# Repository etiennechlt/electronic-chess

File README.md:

# Échiquier électronique automatique à détection LC

Échiquier physique qui identifie chaque pièce (type et couleur) par un
résonateur LC passif logé dans sa base, arbitre les coups (roque,
prise en passant, promotion incluse), joue contre un moteur d'échecs
ou en ligne, et fonctionne sur batterie. Plateau fin de 44 cm et
21 mm d'épaisseur ; le déplacement des pièces par aimant sur portique
CoreXY est une base optionnelle qui se substitue au fond plat. Le
STM32G474 est maître, un ESP32-S3 sert de pont radio (WiFi, BLE vers
l'horloge à bascule séparée), le Raspberry Pi Zero 2 W est optionnel.

## Principe de détection

Chaque pièce porte une bobine plate de 45 µH et un condensateur C0G
1 % de la série E12 qui fixe sa classe (12 valeurs, 217 à 613 kHz).
Chaque case excite en large bande par un front raide, écoute le
ringdown à travers l'entrefer, et classifie au plus proche voisin sur
des fréquences calibrées par pièce. L'aimant de pièce est en ferrite
dure, transparent au champ de mesure ; celui du chariot en néodyme.

## Source de vérité unique

Toute valeur numérique du projet vient de
[`config/board.yaml`](config/board.yaml). Les grandeurs dérivées (les
12 fréquences, diamètres, courses, entrefer, autonomie) sont calculées
par la bibliothèque `chessboard_calc` et épinglées par les tests
contre la spécification. Le pas de case `p` est figé à 50 mm
(ADR 0010) ; tout reste paramétrique et le rapport compare toujours
40 et 50.

```bash
python3 -m venv .venv && .venv/bin/pip install -e ".[dev]"
.venv/bin/pytest                                        # les garde-fous
.venv/bin/python -m chessboard_calc report --pitch all  # tables dérivées
```

Le test de couloir (`tests/test_corridor.py`) verrouille la contrainte
`r_mobile + r_statique <= p/2` pour les 21 paires de classes : si une
édition du yaml la viole, la CI casse, car la partie se bloquerait dès
e2-e4.

## Plateau 8 x 8 (ADR 0010)

Un module plateau invariant (contreplaqué plus quatre quadrants 4 x 4
identiques, frontal analogique embarqué) posé dans une base fine ou,
plus tard, dans une base chariot avec le CoreXY et les ailes de
capture. Cerveau, carte puissance et cellules plates au fond de la
base, sur la même empreinte dans les deux bases. Horloge à bascule
séparée, en BLE. Choix et raisons dans la
[note 10](docs/notes/10-plateau-8x8-et-horloge.md).

| Plateau fin | Vue éclatée |
|---|---|
|  |  |

| Base chariot ouverte | Base chariot avec le module plateau |
|---|---|
|  |  |

| Horloge à bascule | Horloge éclatée |
|---|---|
|  |  |

Vue 3D interactive (bases, éclaté, couches, noms au survol) :
`python mechanical/viewer.py` puis ouvrir `mechanical/exports/plateau-3d.html`.

| Quadrant 4 x 4 généré (`tools/quadgen`) |
|---|
|  |

Spirales, échappées vers la bande de frontal, 32 LED de camp et leur
distribution, connecteur FPC, et dans la bande de 20 mm le frontal
complet (16 cellules, deux ADG1607, décodeurs, chaîne AD8421 et
OPA2810) : [détails](hardware/quadrant/README.md). Le schéma est
dessiné feuille par feuille (fonction, composants et câblage dans la
[note 17](docs/notes/17-quadrant-fonction-et-cablage.md)) ; un
quadrant réduit 2 x 2, même circuit et même bus, sert de banc de mise
au point : [hardware/quadrant-2x2](hardware/quadrant-2x2/README.md).
Ce quadrant réduit et la [carte de banc](hardware/bench/README.md) qui
le pilote sont les deux cartes du plateau dont le routage est fermé,
donc les deux dont les gerbers sont commités
(`*-gerbers.zip`, produits par `tools/gerbers.py`, qui remplit les
pours avant de tracer et refuse toute carte à nets ouverts) : le banc
de la [note 20](docs/notes/20-tuto-banc.md) se commande tel quel. La
[carte analogique de maquette](hardware/mockup-2x2/analog-board/README.md),
gardée comme référence de la chaîne, est fermée elle aussi et porte
son archive. Ce qui se commande, avec quelles options et ce qu'il
manque aux autres cartes : la
[note 23](docs/notes/23-commande-jlcpcb.md). Ce qu'il faut acheter pour
monter le plateau (les 1 399 composants de quatre quadrants et d'un
cerveau, leur prix chez LCSC et chez Mouser, les paniers prêts à
téléverser) : la [fiche d'approvisionnement du plateau](docs/bom-plateau.md),
regénérée par `tools/bomagg.py`.

| Cerveau (STM32G474, 4 couches) | Puissance (3S, BQ24610, BQ76920) |
|---|---|
|  |  |

| Moteurs (deux TMC2209, base chariot) | Horloge (ESP32-S3, 18650, écran) |
|---|---|
|  |  |

Les quatre cartes sortent du générateur générique `tools/boardgen` ;
ce que le routeur laisse ouvert est listé dans le README de chaque
carte et résumé dans la [note 11](docs/notes/11-cartes-du-plateau.md).
Pour ouvrir, vérifier, simuler et tester : [note 13](docs/notes/13-revue-et-verification.md).

## Maquette 2 x 2 (phase 1, conçue, non construite)

La maquette a été conçue de bout en bout puis remplacée par le plateau
direct (ADR 0010) ; elle reste la référence de la chaîne analogique et
du routage ([guide](hardware/mockup-2x2/README.md),
[fiche d'approvisionnement](docs/bom-maquette.md)).

| Vue d'ensemble | Pièce de test éclatée |
|---|---|
|  |  |

- **Carte bobines** (100 x 100, 4 couches, générée par
  [`coilgen`](tools/coilgen/)) : 4 spirales série de 5 tours par
  couche, 8 LED de camp WS2812B chaînées aux coins des cases (deux
  points lumineux par case à travers la surface en bois, ADR 0009).
  Son routage n'est pas fermé et son DRC porte 251 violations
  bloquantes : elle n'a pas d'archive de fabrication, et l'archive
  obsolète qu'elle portait a été retirée
  ([note 22](docs/notes/22-erreurs-de-conception.md), point 10),
  [détails](hardware/mockup-2x2/coil-board/README.md).
- **Carte analogique** (100 x 62, 2 couches, générée par
  [`analoggen`](tools/analoggen/)) : mux différentiel, AD8421,
  filtres Sallen-Key validés ngspice, buck forced-PWM contre LDO en
  cavalier, UART Pi isolée ; routage fermé, zéro élément non connecté
  et zéro erreur bloquante au DRC de KiCad, gerbers commités,
  [détails](hardware/mockup-2x2/analog-board/README.md).
- **Firmware** ([`firmware/board`](firmware/board/)) : les deux
  voies d'extraction du brief mesurées simultanément sur chaque
  ringdown, quatre quadrants par le bus de mux, calibration en flash,
  CSV sur le port série ; compile en CI. Pont radio et horloge en
  ESP-IDF ([`firmware/esp32`](firmware/esp32/)), protocole texte commun
  ([note 12](docs/notes/12-protocole.md)).
- **Mécanique** ([`mechanical/`](mechanical/README.md)) : plateau
  8 x 8 (module, bases, ailes), horloge, pucks de test, gabarits de
  bobinage, STL et STEP paramétriques, rendus et vue interactive.

| Carte bobines | Carte analogique |
|---|---|
|  |  |

## Documentation

La base de connaissances du projet vit dans
[`docs/`](docs/README.md) : entrées par intention, notes de concepts
(mesure, architecture, générateurs, routeur, firmware), état de
référence, runbook de régénération et journal des décisions. Les
décisions formelles sont dans [`docs/adr/`](docs/adr/README.md).

## Arborescence

| Répertoire | Contenu | Phase |
|---|---|---|
| `config/` | `board.yaml`, source de vérité unique | 0 |
| `chessboard_calc/` | calculs paramétriques et garde-fous | 0 |
| `tools/coilgen`, `tools/analoggen` | générateurs KiCad des deux cartes de la maquette | 1 |
| `tools/drc.py`, `tools/plot.py`, `tools/gerbers.py` | DRC, tracés de faces et gerbers de fabrication, par le `pcbnew` de KiCad | 1 à 2 |
| `tools/fabcheck.py`, `tools/bomagg.py` | audit avant commande, et liste d'achat agrégée avec ses prix | 1 à 2 |
| `tools/quadgen`, `hardware/quadrant/` | générateur et projet KiCad du quadrant 4 x 4 | 2 |
| `tools/boardgen`, `hardware/{brain,power,motion,clock}/` | générateur générique et projets KiCad du cerveau, de la puissance, des moteurs et de l'horloge | 2 |
| `hardware/mockup-2x2/` | projets KiCad (`.kicad_pro` à ouvrir), gerbers, BOM, guides | 1 |
| `firmware/mockup/` | firmware Nucleo-G474RE (référence) | 1 |
| `firmware/board/` | firmware du cerveau : bus des quadrants, quatre ADC, 128 LED | 2 |
| `firmware/esp32/` | pont radio, horloge (ESP-IDF, NimBLE), protocole de la note 12, le scanner Hall de la note 24 et la console du démonstrateur Hall + RFID (note 27) | 2 à 3 |
| `tools/taggen`, `hardware/hallrfid-demo/`, `hardware/tag-demo/` | le démonstrateur Hall + RFID : carte à deux cases (par `tools/boardgen`) et planche d'étiquettes NFC, gerbers et BOM | démonstrateur |
| `measurements/` | protocole, gabarits CSV, analyse | 1 |
| `mechanical/` | modèles CadQuery (plateau, horloge, pucks), rendus, vue 3D | 1 à 3 |
| `app/` | application, client Lichess sur le pont | 3 à 4 |

## État et décisions

Socle, calculs et CI livrés ; le plateau 8 x 8 est conçu directement
(ADR 0010) : yaml, géométrie, modèles 3D (STL et STEP dans
`mechanical/exports/`), quadrant complet, cerveau, puissance, moteurs et
horloge générés, firmware du cerveau compilé, pont et horloge écrits ;
premier lot de la phase 1 fait, la revue des cartes
([note 14](docs/notes/14-revue-des-cartes.md) : brochages relus, huit
erreurs corrigées dans les générateurs, DRC KiCad par `tools/drc.py`).
La suite est phasée : **phase 1, tout fonctionne sans chariot** (revue,
simulation, commande, bring-up, mesures, firmware, horloge, appli) ;
**phase 2, le chariot**. Feuille de route dans la
[note 07](docs/notes/07-etat-et-reste-a-faire.md). L'alternative
« Hall + RFID » (un capteur par case, une étiquette par pièce) a été
évaluée et prototypée comme étape intermédiaire dans la
[note 24](docs/notes/24-hall-et-rfid.md). Deux démonstrateurs de table,
un par technologie, cartes de 100 x 100 mm prêtes pour JLCPCB,
nomenclatures chiffrées et tutoriels complets, sont décrits dans les
notes [26](docs/notes/26-demonstrateur-lc.md) (oscillations LC) et
[27](docs/notes/27-demonstrateur-hall-rfid.md) (Hall et RFID). Les
décisions d'architecture et leurs justifications sont dans
[`docs/adr/`](docs/adr/README.md) ; conventions dans
[`CLAUDE.md`](CLAUDE.md) : code et commentaires en anglais,
documentation en français, aucune valeur dupliquée hors de
`board.yaml`.

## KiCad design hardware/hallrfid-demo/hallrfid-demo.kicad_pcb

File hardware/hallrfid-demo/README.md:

# Démonstrateur Hall + RFID : la carte à deux cases

Carte générée par `tools/boardgen` (module `hallrfid`) depuis
`config/board.yaml` (section `hall_rfid.demo`, qui lit tout ce que
`hall_rfid.mockup` fixe déjà : capteur, boucles, adaptation, étiquettes,
critères) et le modèle `chessboard_calc.hallrfid_demo`. 100 x 100 mm,
4 couches : F.Cu composants et signaux, In1 plan de masse borné à la
bande (aucun cuivre de masse à moins de 4 mm d'une boucle, D12), In2
alimentations et liaisons longues avec la dorsale 3,3 V le long des
bords ouest et sud, B.Cu signaux, le pont de chaque boucle et les
amorces des couloirs de capteurs. Ne pas éditer les fichiers KiCad à la main : modifier le yaml ou
le générateur, puis regénérer. Le rôle de chaque composant, l'assemblage
et les tests sont dans la [note 27](../../docs/notes/27-demonstrateur-hall-rfid.md).

## Blocs

- **Zone de jeu** (y de 0 à 50 mm, au pas de 50) : deux boucles NFC
  dessinées dans le cuivre de la face avant, L60x3 sur A1 (3 spires de
  30 mm) et L70x2 sur B1 (2 spires de 35 mm), chacune refermée par un
  « net tie » et un pont sur la face arrière ; six capteurs Hall
  DRV5055A3 (le centre de chaque case, l'amas de quatre autour du centre
  de A1) avec leur 100 nF et leur filtre RC (1 kΩ près du capteur, 10 nF
  à l'arrivée dans la bande), leurs trios de pistes sortant par le
  couloir réservé au sud-ouest de chaque ouverture. Rien d'autre n'y
  passe : le routeur a la zone fermée hors des boucles.
- **Deux lecteurs MFRC522** (HVQFN-32) dans la bande, chacun sous sa
  boucle : quartz 27,12 MHz, réseau d'adaptation symétrique par côté
  (0 Ω isolateur, L0 560 nH, C0 220 pF, C1 et C2 en valeur principale
  plus complément E12, emplacements de retouche non montés, Rq), points
  de test TX1 et TX2 où un pigtail de NanoVNA se soude, 1 Ω dans TVDD
  avec ses points de test, diviseur de réception à seconde R1 non montée et cavalier à
  souder (D15), points de test TX1, TX2, RX, masse. Valeurs de
  `nfc.matching` : sur A1 Rq 0,68 Ω, C1 56 + 5,6 pF, C2 470 + 33 pF, R1
  3,9 kΩ ; sur B1 Rq 0,47 Ω, C1 82 + 3,3 pF, C2 680 + 56 pF, R1 3,3 kΩ.
- **Chaîne Hall** : CD74HC4067 (capteurs sur les voies 0, 1 et 4 à 7,
  masse en 8, rail divisé par deux en 9, échelon de la LED en 10, les
  voies 11 à 15 sur la barrette J3), rail des capteurs commuté par un
  AO3401A avec cavalier de dérivation, les deux capteurs centraux aussi
  sur une entrée ADC directe.
- **ESP32-S3-WROOM-1-N8** à USB natif (USB-C GCT USB4085, USBLC6-2,
  5,1 kΩ sur CC), antenne sur le bord est sans cuivre dessous, boutons
  EN et BOOT, LED, points de test UART0, barrette d'échappement 2 x 10
  non montée pour une DevKitC ; AMS1117-3.3 avec sa charge tantale ;
  tampon MISO 74LVC125 avec ses 0 Ω de contournement non montés ;
  entrée PICKUP de la vignette de champ.
- Six trous M3 non métallisés (coins de la zone de jeu et de la bande),
  trois mires d'assemblage dans la bande.

## Brochage de l'ESP32-S3

`hall_rfid.demo.esp32.pins` du yaml, repris dans l'en-tête généré du
micrologiciel (`firmware/esp32/hallrfid-demo/main/demo_config.h`) et
vérifié par `tests/test_hallrfid_demo.py` (entrées analogiques sur
l'ADC1, aucune broche de démarrage ni de PSRAM).

## Ouvrir

`hallrfid-demo.kicad_pro` est le fichier à ouvrir dans KiCad 7 : il
associe le schéma généré et la carte, et porte les règles du routeur.
Classe de nets : garde 0,15 mm, piste 0,3 mm (0,5 mm pour VBUS, 3V3 et
le rail des capteurs), vias 0,8/0,4 mm. Les bibliothèques propres au
projet (symbole du MFRC522, net tie des boucles) sont dans
`hardware/lib/`, déclarées dans le projet.

## Générer et vérifier

```bash
PYTHONPATH=tools .venv/bin/python -m boardgen build hallrfid-demo --render docs/images/hallrfid-demo.png
/usr/bin/python3 tools/drc.py hardware/hallrfid-demo/hallrfid-demo.kicad_pcb
/usr/bin/python3 tools/gerbers.py hardware/hallrfid-demo/hallrfid-demo.kicad_pcb
python3 tools/fabcheck.py hardware/hallrfid-demo
cd hardware/hallrfid-demo && sha256sum -c hallrfid-demo-gerbers.sha256
```

Le build dessine d'abord les deux boucles et leurs amenées à la main
(`boardgen.nfcloop`), ferme la zone de jeu au routeur hors des boucles
et des couloirs, route les trios des capteurs en premier, puis le reste
(alimentations en large, signaux en fin), reprend les liaisons murées
par trois tours de dérouté, et finit en géométrie exacte comme les
autres cartes du dépôt (note 04).

## État

Fermée le 18/10/2026, au dix-neuvième build, par `boardgen build
hallrfid-demo` sur le yaml commité :

| Contrôle | Résultat |
|---|---|
| Build | 162 composants, 87 liaisons routées, 0 ouverte, 0 défaut de garde du générateur ; 1624 segments, 413 vias, 14 jonctions de la passe de finition |
| DRC KiCad 7.0.11 | 0 erreur, 0 élément non connecté ; 529 avertissements ignorés : recouvrements de sérigraphie (références sur les pastilles des 0603 serrés), chemins de bibliothèque, et les amorces d'échappement et vias de sortie non prolongés que le routeur laisse derrière lui |
| Archive | `hallrfid-demo-gerbers.zip`, 10 couches, 13 fichiers ; `hallrfid-demo-gerbers.sha256` lie l'archive au `.kicad_pcb` commité |
| `fabcheck` | « bare boards ready » : 99 des 143 composants montés ont un code LCSC ; les 22 lignes sans code sont les condensateurs C0G des réseaux d'adaptation (56, 5,6, 470, 33, 82, 3,3, 680 pF et les emplacements de retouche), le tantale et la puce du net tie, à relever au panier avant un ordre d'assemblage (note 23, paragraphe 5) |

Ce qu'il a fallu pour fermer la carte, et que le générateur garde :
quatre couches ; la zone de jeu fermée au routeur hors des boucles ;
une amorce par liaison dans chaque couloir de capteurs ; les rangées
d'adaptation au pas de 2,5 mm avec leurs nœuds alignés ; un anneau
libre de 5,2 mm autour des puces à pas fin pour leurs vias
d'échappement ; une dorsale 3,3 V large sur la couche interne le long
des bords ouest et sud ; les règles de la capacité quatre couches de
JLCPCB (0,25 mm, garde 0,127 mm, vias 0,6/0,3 mm) ; et une recherche
A* plus gourmande (poids 2,5) pour les liaisons longues.

## Nomenclatures

`bom.csv` liste tout, montés et non montés ; `jlc-bom.csv` et
`jlc-cpl.csv` ne portent que les lignes à code LCSC des composants
montés, pour l'assemblage Standard face avant (le module et le MFRC522
sont des pièces étendues). Les codes des passifs sont des basiques
JLCPCB, à vérifier à l'aperçu de la commande ; les non montés
(emplacements de retouche, seconde R1, 0 Ω de contournement, barrette
d'échappement) sont exclus. La nomenclature chiffrée avec liens et
prix, planche d'étiquettes comprise, est
[`docs/bom-demonstrateur-b.md`](../../docs/bom-demonstrateur-b.md).

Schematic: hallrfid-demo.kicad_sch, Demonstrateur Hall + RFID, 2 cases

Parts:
C11, C12, C13, C14, C15, C16, C31, C42, C52, C63, C71, C103, C104, C105, C106, C108, C203, C204, C205, C206, C208: 100n; C_0603_1608Metric; LCSC C14663
C21, C22, C23, C24, C25, C26, C32, C54: 10n; C_0603_1608Metric; LCSC C57112
C41, C53, C109, C209: 1u; C_0603_1608Metric; LCSC C15849
C51, C61, C107, C207: 10u/25V; C_1206_3216Metric; LCSC C13585
C62: 22u/10V tantale; CP_EIA-3528-21_Kemet-B; MPN TAJB226K010RNJ
C101, C102, C201, C202: 15p; C_0603_1608Metric; LCSC C1644
C111, C121, C211, C221: 220p; C_0603_1608Metric; LCSC C1653
C112, C122, C216, C226: 56p; C_0603_1608Metric
C113, C123: 5p6; C_0603_1608Metric
C114, C117, C124, C127, C214, C217, C224, C227: retouche; C_0603_1608Metric; not fitted
C115, C125: 470p; C_0603_1608Metric
C116, C126: 33p; C_0603_1608Metric
C131, C231: 1n; C_0603_1608Metric; LCSC C1588
C212, C222: 82p; C_0603_1608Metric
C213, C223: 3p3; C_0603_1608Metric
C215, C225: 680p; C_0603_1608Metric
D1: LED; LED_0603_1608Metric; MPN 19-217/GHC-YR1S2/3T; LCSC C72043
J1: USB-C; USB_C_Receptacle_GCT_USB4085; MPN USB4085-GF-A; LCSC C2988369
J2: 5V BENCH; PinHeader_1x02_P2.54mm_Vertical
J3: MUX EXT; PinHeader_1x06_P2.54mm_Vertical
J4: ESCAPE; PinHeader_2x10_P2.54mm_Vertical; not fitted
J5: PICKUP; PinHeader_1x03_P2.54mm_Vertical
JP1: HALL_VCC bypass; SolderJumper-2_P1.3mm_Open_Pad1.0x1.5mm
JP101, JP201: R1b bypass; SolderJumper-2_P1.3mm_Bridged_Pad1.0x1.5mm
L1: boucle L60x3; NetTie_NFC_Loop
L2: boucle L70x2; NetTie_NFC_Loop
L111, L121, L211, L221: 560n; L_0805_2012Metric; MPN FHW0805UCR56JGT; LCSC C139264
Q1: AO3401A; SOT-23; MPN AO3401A; LCSC C15127
R11, R12, R13, R14, R15, R16, R53, R133, R233: 1k; R_0603_1608Metric; LCSC C21190
R31, R111, R121, R211, R221: 0R; R_0603_1608Metric; LCSC C21189
R32, R33, R34, R35, R41, R51, R52, R71, R141, R142, R241, R242: 10k; R_0603_1608Metric; LCSC C25804
R61, R62: 5k1; R_0603_1608Metric; LCSC C23186
R101, R201: 1R; R_0603_1608Metric
R112, R122: 0R68; R_0603_1608Metric
R131: 3k9; R_0603_1608Metric
R132: 3k9; R_0603_1608Metric; not fitted
R143, R243: 0R; R_0603_1608Metric; LCSC C21189; not fitted
R212, R222: 0R47; R_0603_1608Metric
R231: 3k3; R_0603_1608Metric
R232: 3k3; R_0603_1608Metric; not fitted
SW1: BOOT; SW_SPST_PTS645; MPN PTS645SM43SMTR92; LCSC C221929
SW2: EN; SW_SPST_PTS645; MPN PTS645SM43SMTR92; LCSC C221929
TP1: 3V3; TestPoint_Pad_1.5x1.5mm
TP2, TP7, TP105, TP205: GND; TestPoint_Pad_1.5x1.5mm
TP3: VBUS; TestPoint_Pad_1.5x1.5mm
TP4: HALL_VCC; TestPoint_Pad_1.5x1.5mm
TP5: UART0_TX; TestPoint_Pad_1.5x1.5mm
TP6: UART0_RX; TestPoint_Pad_1.5x1.5mm
TP101: TX1_A1; TestPoint_Pad_1.5x1.5mm
TP102: TX2_A1; TestPoint_Pad_1.5x1.5mm
TP103: RX_A1; TestPoint_Pad_1.5x1.5mm
TP104: TVDD_A1; TestPoint_Pad_1.5x1.5mm
TP201: TX1_B1; TestPoint_Pad_1.5x1.5mm
TP202: TX2_B1; TestPoint_Pad_1.5x1.5mm
TP203: RX_B1; TestPoint_Pad_1.5x1.5mm
TP204: TVDD_B1; TestPoint_Pad_1.5x1.5mm
U1, U2: MFRC52202HN1,151; HVQFN-32-1EP_5x5mm_P0.5mm_EP3.1x3.1mm; MPN MFRC52202HN1,151; LCSC C11322
U3: CD74HC4067; SSOP-24_5.3x8.2mm_P0.65mm; MPN CD74HC4067SM96; LCSC C98457
U4: ESP32-S3-WROOM-1-N8; ESP32-S3-WROOM-1; MPN ESP32-S3-WROOM-1-N8; LCSC C2913204
U5: USBLC6-2; SOT-23-6; MPN USBLC6-2SC6; LCSC C7519
U6: AMS1117-3.3; SOT-223-3_TabPin2; MPN AMS1117-3.3; LCSC C6186
U7: 74LVC125; TSSOP-14_4.4x5mm_P0.65mm; MPN 74LVC125APW,118; LCSC C6059
U11, U12, U13, U14, U15, U16: DRV5055A3; SOT-23; MPN DRV5055A3QDBZR; LCSC C266128
Y1, Y2: 27.12MHz; Crystal_SMD_3225-4Pin_3.2x2.5mm; MPN X32252712MMB4SI; LCSC C29975

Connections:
3V3: C31.1, C51.1, C52.1, C62.1, C63.1, C71.1, C103.1, C104.1, C105.1, C109.1, C203.1, C204.1, C205.1, C209.1, J4.1, J5.3, JP1.1 (A), Q1.2 (S), R41.2, R51.2, R52.2, R71.2, R101.1, R141.2, R201.1, R241.2, TP1.1, U1.2 (PVDD), U1.3 (DVDD), U1.9 (SVDD), U1.15 (AVDD), U1.32 (EA), U2.2 (PVDD), U2.3 (DVDD), U2.9 (SVDD), U2.15 (AVDD), U2.32 (EA), U3.24 (VCC), U4.2 (3V3), U6.2 (VO), U7.10, U7.13, U7.14 (VCC)
CC1: J1.A5 (CC1), R61.1
CC2: J1.B5 (CC2), R62.1
ESP_EN: C53.1, R51.1, SW2.1, U4.3 (EN)
ESP_IO0: R52.1, SW1.1, U4.27 (IO0)
EXT11: J3.1, U3.20 (I11)
EXT12: J3.2, U3.19 (I12)
EXT13: J3.3, U3.18 (I13)
EXT14: J3.4, U3.17 (I14)
EXT15: J3.5, U3.16 (I15)
GND: C11.2, C12.2, C13.2, C14.2, C15.2, C16.2, C21.2, C22.2, C23.2, C24.2, C25.2, C26.2, C31.2, C32.2, C41.2, C42.2, C51.2, C52.2, C53.2, C54.2, C61.2, C62.2, C63.2, C71.2, C101.2, C102.2, C103.2, C104.2, C105.2, C106.2, C107.2, C108.2, C109.2, C111.2, C115.2, C116.2, C117.2, C121.2, C125.2, C126.2, C127.2, C201.2, C202.2, C203.2, C204.2, C205.2, C206.2, C207.2, C208.2, C209.2, C211.2, C215.2, C216.2, C217.2, C221.2, C225.2, C226.2, C227.2, D1.1 (K), J1.A1 (GND), J1.A12 (GND), J1.B1 (GND), J1.B12 (GND), J1.S1 (SHIELD), J2.2, J3.6, J4.2, J5.2, R31.2, R33.2, R35.2, R61.2, R62.2, R142.2, R242.2, SW1.2, SW2.2, TP2.1, TP7.1, TP105.1, TP205.1, U1.1 (I2C), U1.4 (DVSS), U1.5 (PVSS), U1.7 (MFIN), U1.10 (TVSS), U1.14 (TVSS), U1.18 (AVSS), U1.33 (EP), U2.1 (I2C), U2.4 (DVSS), U2.5 (PVSS), U2.7 (MFIN), U2.10 (TVSS), U2.14 (TVSS), U2.18 (AVSS), U2.33 (EP), U3.6 (I3), U3.7 (I2), U3.12 (GND), U3.23 (I8), U4.1 (GND), U4.40 (GND), U4.41 (GND), U5.2 (GND), U6.1 (GND), U7.7 (GND), U7.9, U7.12, U11.3 (GND), U12.3 (GND), U13.3 (GND), U14.3 (GND), U15.3 (GND), U16.3 (GND), Y1.2, Y1.4, Y2.2, Y2.4
HALL_A1: C21.1, J4.17, R11.2, U3.9 (I0), U4.38 (IO2)
HALL_B1: C22.1, J4.18, R12.2, U3.8 (I1), U4.4 (IO4)
HALL_VCC: C11.1, C12.1, C13.1, C14.1, C15.1, C16.1, C41.1, C42.1, JP1.2 (B), Q1.3 (D), R32.1, TP4.1, U11.1 (VCC), U12.1 (VCC), U13.1 (VCC), U14.1 (VCC), U15.1 (VCC), U16.1 (VCC)
HC4: C23.1, R13.2, U3.5 (I4)
HC5: C24.1, R14.2, U3.4 (I5)
HC6: C25.1, R15.2, U3.3 (I6)
HC7: C26.1, R16.2, U3.2 (I7)
HOUT_HALL_A1: R11.1, U11.2 (OUT)
HOUT_HALL_B1: R12.1, U12.2 (OUT)
HOUT_HC4: R13.1, U13.2 (OUT)
HOUT_HC5: R14.1, U14.2 (OUT)
HOUT_HC6: R15.1, U15.2 (OUT)
HOUT_HC7: R16.1, U16.2 (OUT)
LED: J4.20, R34.1, R53.1, U4.12 (IO8)
LED_A: D1.2 (A), R53.2
LED_STEP: C32.1, R34.2, R35.1, U3.21 (I10)
LOOP_A1_1: L1.1, R122.2
LOOP_A1_2: L1.2, R112.2
LOOP_B1_1: L2.1, R222.2
LOOP_B1_2: L2.2, R212.2
MISO_A1: R143.1, U1.31 (D7/MISO/SCL), U7.2
MISO_B1: R243.1, U2.31 (D7/MISO/SCL), U7.5
MUX_EN: R31.1, U3.15 (~E)
MUX_OUT: J4.11, U3.1 (COM), U4.39 (IO1)
MUX_S0: J4.12, U3.10 (S0), U4.8 (IO15)
MUX_S1: J4.13, U3.11 (S1), U4.9 (IO16)
MUX_S2: J4.14, U3.14 (S2), U4.10 (IO17)
MUX_S3: J4.15, U3.13 (S3), U4.11 (IO18)
NEA_A1: C111.1, C112.1, C113.1, C114.1, L111.2
NEA_B1: C211.1, C212.1, C213.1, C214.1, L211.2
NEB_A1: C112.2, C113.2, C114.2, C115.1, C116.1, C117.1, R112.1
NEB_B1: C212.2, C213.2, C214.2, C215.1, C216.1, C217.1, R212.1
NEF_A1: L111.1, R111.2
NEF_B1: L211.1, R211.2
NRSTPD_A1: J4.8, R142.1, U1.6 (NRSTPD), U4.23 (IO21)
NRSTPD_B1: J4.9, R242.1, U2.6 (NRSTPD), U4.24 (IO47)
NSS_A1: J4.6, R141.1, U1.24 (SDA/NSS/RX), U4.22 (IO14), U7.1
NSS_B1: J4.7, R241.1, U2.24 (SDA/NSS/RX), U4.31 (IO38), U7.4
NWA_A1: C121.1, C122.1, C123.1, C124.1, L121.2, R131.1
NWA_B1: C221.1, C222.1, C223.1, C224.1, L221.2, R231.1
NWB_A1: C122.2, C123.2, C124.2, C125.1, C126.1, C127.1, R122.1
NWB_B1: C222.2, C223.2, C224.2, C225.1, C226.1, C227.1, R222.1
NWF_A1: L121.1, R121.2
NWF_B1: L221.1, R221.2
PICKUP: C54.1, J4.19, J5.1, U4.5 (IO5)
RAIL_HALF: R32.2, R33.1, U3.22 (I9)
RFID_IRQ: J4.10, R71.1, U1.23 (IRQ), U2.23 (IRQ), U4.17 (IO9)
ROW_EN1: J4.16, Q1.1 (G), R41.1, U4.18 (IO10)
RXC_A1: C131.1, JP101.2 (B), R132.2
RXC_B1: C231.1, JP201.2 (B), R232.2
RXD_A1: JP101.1 (A), R131.2, R132.1
RXD_B1: JP201.1 (A), R231.2, R232.1
RX_A1: C131.2, R133.1, TP103.1, U1.17 (RX)
RX_B1: C231.2, R233.1, TP203.1, U2.17 (RX)
SPI_MISO: J4.5, R143.2, R243.2, U4.21 (IO13), U7.3, U7.6
SPI_MOSI: J4.3, U1.30 (D6/MOSI), U2.30 (D6/MOSI), U4.19 (IO11)
SPI_SCK: J4.4, U1.29 (D5/SCK), U2.29 (D5/SCK), U4.20 (IO12)
TVDD_A1: C107.1, C108.1, R101.2, TP104.1, U1.12 (TVDD)
TVDD_B1: C207.1, C208.1, R201.2, TP204.1, U2.12 (TVDD)
TX1_A1: R111.1, TP101.1, U1.11 (TX1)
TX1_B1: R211.1, TP201.1, U2.11 (TX1)
TX2_A1: R121.1, TP102.1, U1.13 (TX2)
TX2_B1: R221.1, TP202.1, U2.13 (TX2)
UART0_RX: TP6.1, U4.36 (RXD0)
UART0_TX: TP5.1, U4.37 (TXD0)
USB_DM: U4.13 (IO19), U5.6 (I/O1)
USB_DM_C: J1.A7 (D-), J1.B7 (D-), U5.1 (I/O1)
USB_DP: U4.14 (IO20), U5.4 (I/O2)
USB_DP_C: J1.A6 (D+), J1.B6 (D+), U5.3 (I/O2)
VBUS: C61.1, J1.A4 (VBUS), J1.A9 (VBUS), J1.B4 (VBUS), J1.B9 (VBUS), J2.1, TP3.1, U5.5 (VBUS), U6.3 (VI)
VMID_A1: C106.1, R133.2, U1.16 (VMID)
VMID_B1: C206.1, R233.2, U2.16 (VMID)
XI_A1: C101.1, U1.21 (OSCIN), Y1.1
XI_B1: C201.1, U2.21 (OSCIN), Y2.1
XO_A1: C102.1, U1.22 (OSCOUT), Y1.3
XO_B1: C202.1, U2.22 (OSCOUT), Y2.3

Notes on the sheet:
READER A1, LOOP, MATCHING
READER B1, LOOP, MATCHING
HALL SENSORS
MULTIPLEXER, REFERENCES, SWITCHED RAIL
ESP32-S3, USB, 3.3 V
MISO BUFFER, HEADERS, TEST POINTS

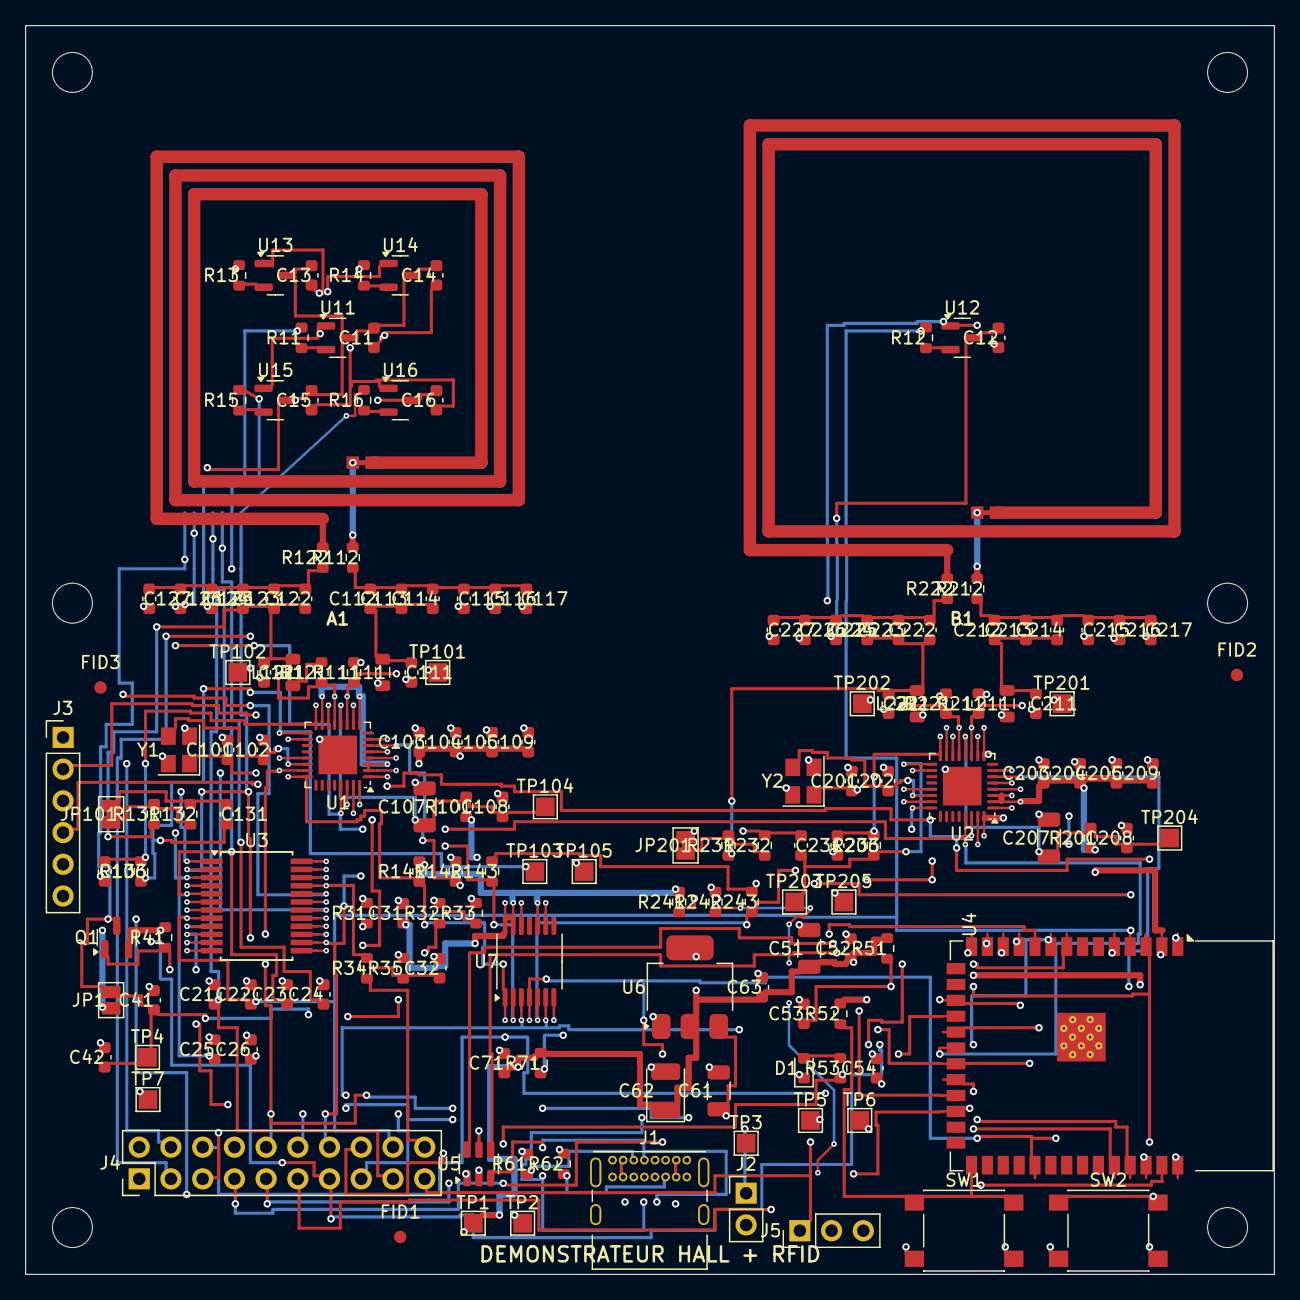
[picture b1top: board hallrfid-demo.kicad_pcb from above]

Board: 4 copper layers, 100.0 x 100.0 mm, 171 parts (0 on the bottom side), 87 nets.

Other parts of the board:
FID1, FID2, FID3: Fiducial; Fiducial_1mm_Mask2mm
H: NPTH; NPTH_3.2
H#2, H#3, H#4, H#5, H#6: NPTH; NPTH_3.2

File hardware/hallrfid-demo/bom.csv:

References,Qty,Value,Footprint,MPN,LCSC,DNP
C101 C102 C201 C202,4,15p,C_0603_1608Metric,,C1644,
C111 C121 C211 C221,4,220p,C_0603_1608Metric,,C1653,
C112 C122 C216 C226,4,56p,C_0603_1608Metric,,,
C113 C123,2,5p6,C_0603_1608Metric,,,
C114 C117 C124 C127 C214 C217 C224 C227,8,retouche,C_0603_1608Metric,,,DNP
C115 C125,2,470p,C_0603_1608Metric,,,
C116 C126,2,33p,C_0603_1608Metric,,,
C131 C231,2,1n,C_0603_1608Metric,,C1588,
C21 C22 C23 C24 C25 C26 C32 C54,8,10n,C_0603_1608Metric,,C57112,
C212 C222,2,82p,C_0603_1608Metric,,,
C213 C223,2,3p3,C_0603_1608Metric,,,
C215 C225,2,680p,C_0603_1608Metric,,,
C109 C209 C41 C53,4,1u,C_0603_1608Metric,,C15849,
C107 C207 C51 C61,4,10u/25V,C_1206_3216Metric,,C13585,
C62,1,22u/10V tantale,CP_EIA-3528-21_Kemet-B,TAJB226K010RNJ,,
C103 C104 C105 C106 C108 C11 C12 C13 C14 C15 C16 C203 C204 C205 C206 C208 C31 C42 C52 C63 C71,21,100n,C_0603_1608Metric,,C14663,
D1,1,LED,LED_0603_1608Metric,19-217/GHC-YR1S2/3T,C72043,
J1,1,USB-C,USB_C_Receptacle_GCT_USB4085,USB4085-GF-A,C2988369,
J2,1,5V BENCH,PinHeader_1x02_P2.54mm_Vertical,,,
J3,1,MUX EXT,PinHeader_1x06_P2.54mm_Vertical,,,
J4,1,ESCAPE,PinHeader_2x10_P2.54mm_Vertical,,,DNP
J5,1,PICKUP,PinHeader_1x03_P2.54mm_Vertical,,,
JP1,1,HALL_VCC bypass,SolderJumper-2_P1.3mm_Open_Pad1.0x1.5mm,,,
JP101 JP201,2,R1b bypass,SolderJumper-2_P1.3mm_Bridged_Pad1.0x1.5mm,,,
L1,1,boucle L60x3,NetTie_NFC_Loop,,,
L111 L121 L211 L221,4,560n,L_0805_2012Metric,FHW0805UCR56JGT,C139264,
L2,1,boucle L70x2,NetTie_NFC_Loop,,,
Q1,1,AO3401A,SOT-23,AO3401A,C15127,
R101 R201,2,1R,R_0603_1608Metric,,,
R112 R122,2,0R68,R_0603_1608Metric,,,
R131,1,3k9,R_0603_1608Metric,,,
R132,1,3k9,R_0603_1608Metric,,,DNP
R143 R243,2,0R,R_0603_1608Metric,,C21189,DNP
R212 R222,2,0R47,R_0603_1608Metric,,,
R231,1,3k3,R_0603_1608Metric,,,
R232,1,3k3,R_0603_1608Metric,,,DNP
R111 R121 R211 R221 R31,5,0R,R_0603_1608Metric,,C21189,
R141 R142 R241 R242 R32 R33 R34 R35 R41 R51 R52 R71,12,10k,R_0603_1608Metric,,C25804,
R11 R12 R13 R133 R14 R15 R16 R233 R53,9,1k,R_0603_1608Metric,,C21190,
R61 R62,2,5k1,R_0603_1608Metric,,C23186,
SW1,1,BOOT,SW_SPST_PTS645,PTS645SM43SMTR92,C221929,
SW2,1,EN,SW_SPST_PTS645,PTS645SM43SMTR92,C221929,
TP1,1,3V3,TestPoint_Pad_1.5x1.5mm,,,
TP101,1,TX1_A1,TestPoint_Pad_1.5x1.5mm,,,
TP102,1,TX2_A1,TestPoint_Pad_1.5x1.5mm,,,
TP103,1,RX_A1,TestPoint_Pad_1.5x1.5mm,,,
TP104,1,TVDD_A1,TestPoint_Pad_1.5x1.5mm,,,
TP105 TP2 TP205 TP7,4,GND,TestPoint_Pad_1.5x1.5mm,,,
TP201,1,TX1_B1,TestPoint_Pad_1.5x1.5mm,,,
TP202,1,TX2_B1,TestPoint_Pad_1.5x1.5mm,,,
TP203,1,RX_B1,TestPoint_Pad_1.5x1.5mm,,,
TP204,1,TVDD_B1,TestPoint_Pad_1.5x1.5mm,,,
TP3,1,VBUS,TestPoint_Pad_1.5x1.5mm,,,
TP4,1,HALL_VCC,TestPoint_Pad_1.5x1.5mm,,,
TP5,1,UART0_TX,TestPoint_Pad_1.5x1.5mm,,,
TP6,1,UART0_RX,TestPoint_Pad_1.5x1.5mm,,,
U1 U2,2,"MFRC52202HN1,151",HVQFN-32-1EP_5x5mm_P0.5mm_EP3.1x3.1mm,"MFRC52202HN1,151",C11322,
U11 U12 U13 U14 U15 U16,6,DRV5055A3,SOT-23,DRV5055A3QDBZR,C266128,
U3,1,CD74HC4067,SSOP-24_5.3x8.2mm_P0.65mm,CD74HC4067SM96,C98457,
U4,1,ESP32-S3-WROOM-1-N8,ESP32-S3-WROOM-1,ESP32-S3-WROOM-1-N8,C2913204,
U5,1,USBLC6-2,SOT-23-6,USBLC6-2SC6,C7519,
U6,1,AMS1117-3.3,SOT-223-3_TabPin2,AMS1117-3.3,C6186,
U7,1,74LVC125,TSSOP-14_4.4x5mm_P0.65mm,"74LVC125APW,118",C6059,
Y1 Y2,2,27.12MHz,Crystal_SMD_3225-4Pin_3.2x2.5mm,X32252712MMB4SI,C29975,

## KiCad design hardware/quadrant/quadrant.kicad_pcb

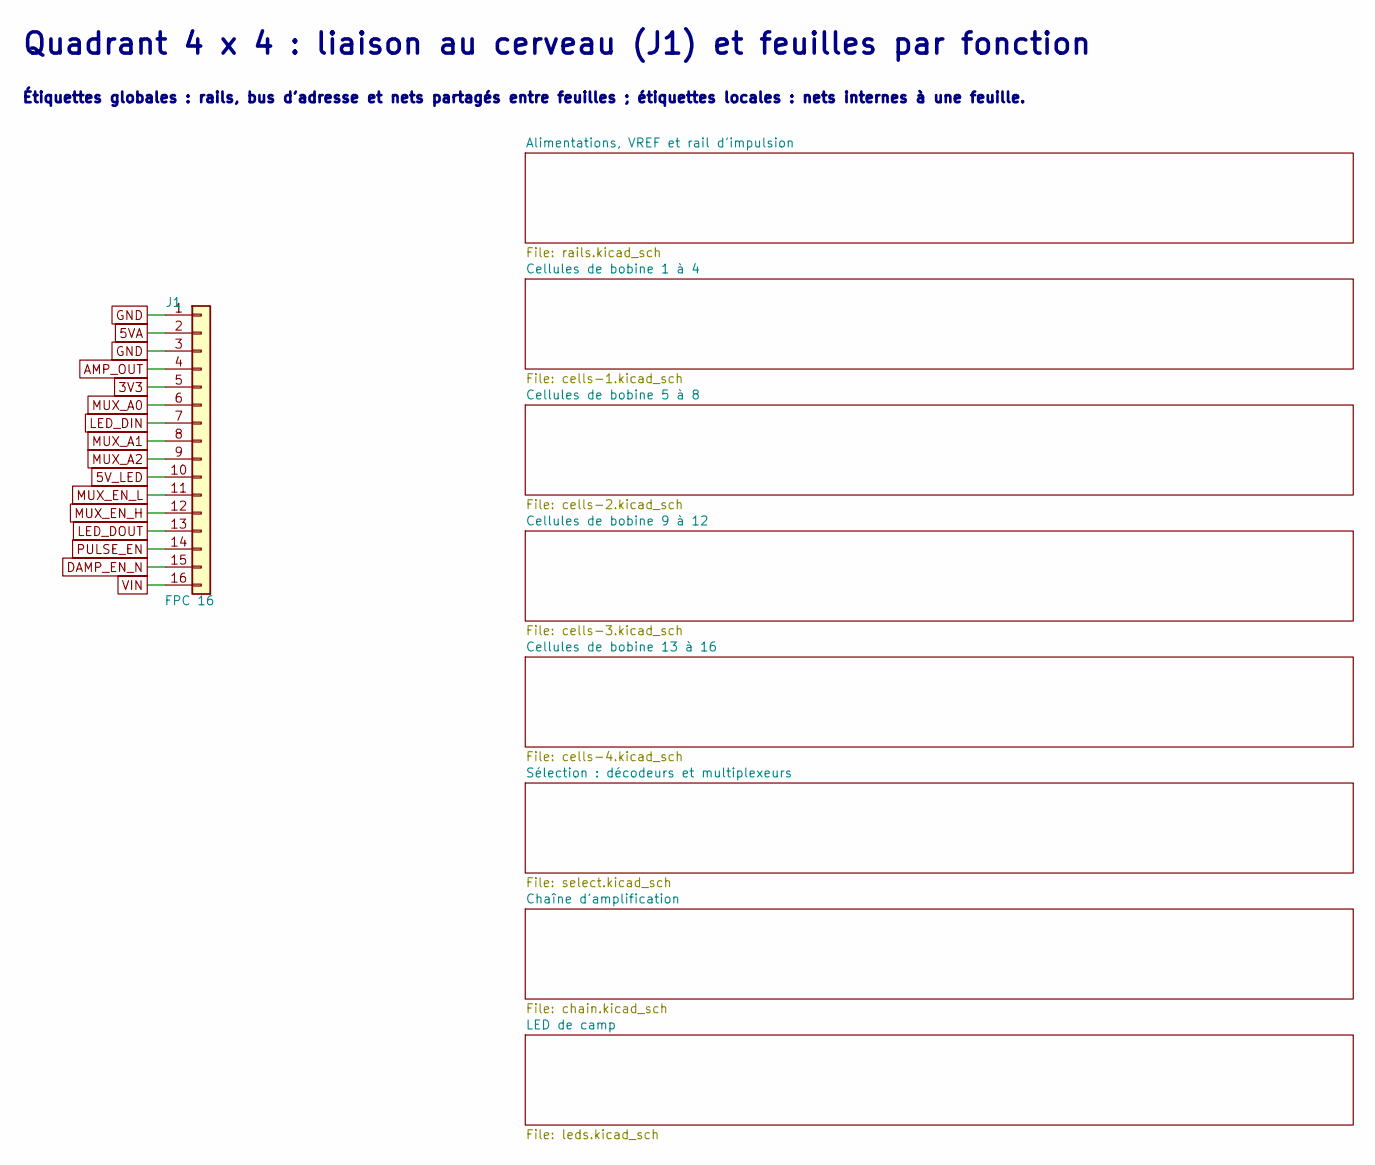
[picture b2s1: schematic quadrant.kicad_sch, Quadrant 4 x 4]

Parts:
J1: FPC 16; Hirose_FH12-16S-0.5SH_1x16-1MP_P0.50mm_Horizontal; MPN FH12-16S-0.5SH(55); LCSC C2837584

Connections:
3V3: J1.5; also elsewhere on the board
5VA: J1.2; also elsewhere on the board
5V_LED: J1.10; also elsewhere on the board
AMP_OUT: J1.4; also elsewhere on the board
DAMP_EN_N: J1.15; also elsewhere on the board
GND: J1.1, J1.3, J1.MP; also elsewhere on the board
LED_DIN: J1.7; also elsewhere on the board
LED_DOUT: J1.13; also elsewhere on the board
MUX_A0: J1.6; also elsewhere on the board
MUX_A1: J1.8; also elsewhere on the board
MUX_A2: J1.9; also elsewhere on the board
MUX_EN_H: J1.12; also elsewhere on the board
MUX_EN_L: J1.11; also elsewhere on the board
PULSE_EN: J1.14; also elsewhere on the board
VIN: J1.16; also elsewhere on the board

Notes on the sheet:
Quadrant 4 x 4 : liaison au cerveau (J1) et feuilles par fonction
Étiquettes globales : rails, bus d'adresse et nets partagés entre feuilles ; étiquettes locales : nets internes à une feuille.

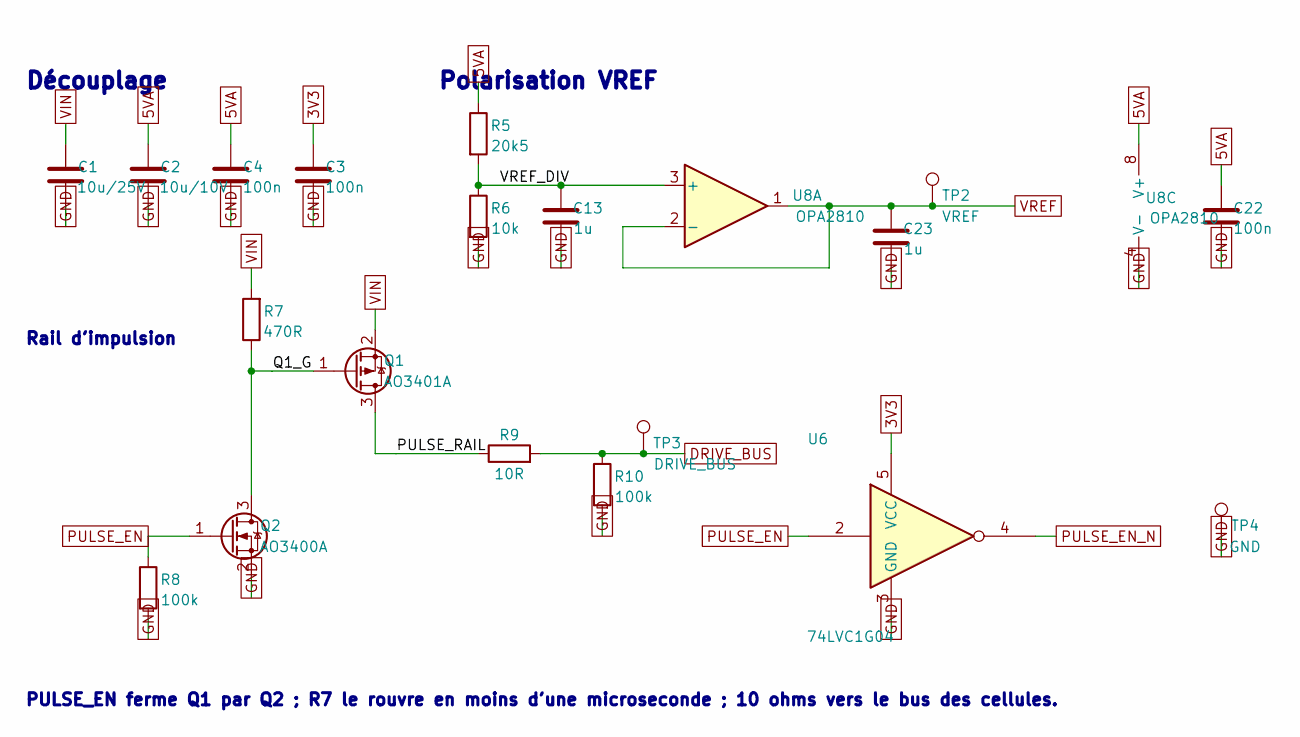
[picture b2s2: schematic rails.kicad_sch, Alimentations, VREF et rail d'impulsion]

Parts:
C1: 10u/25V; C_1206_3216Metric
C2: 10u/10V; C_1206_3216Metric
C3, C4, C22: 100n; C_0603_1608Metric
C13, C23: 1u; C_0603_1608Metric
Q1: AO3401A; SOT-23; MPN AO3401A; LCSC C15127
Q2: AO3400A; SOT-23; MPN AO3400A; LCSC C20917
R5: 20k5; R_0603_1608Metric
R6: 10k; R_0603_1608Metric
R7: 470R; R_0603_1608Metric
R8, R10: 100k; R_0603_1608Metric
R9: 10R; R_2010_5025Metric
TP2: VREF; TestPoint_Pad_1.5x1.5mm
TP3: DRIVE_BUS; TestPoint_Pad_1.5x1.5mm
TP4: GND; TestPoint_Pad_1.5x1.5mm
U6: 74LVC1G04; SOT-23-5; MPN SN74LVC1G04DBVR; LCSC C7477
U8: OPA2810; SOIC-8_3.9x4.9mm_P1.27mm; MPN OPA2810IDR; LCSC C2059830

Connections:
3V3: C3.1, U6.5 (VCC); also elsewhere on the board
5VA: C2.1, C4.1, C22.1, R5.1, U8.8 (V+); also elsewhere on the board
DRIVE_BUS: R9.2, R10.1, TP3.1; also elsewhere on the board
GND: C1.2, C2.2, C3.2, C4.2, C13.2, C22.2, C23.2, Q2.2 (S), R6.2, R8.2, R10.2, TP4.1, U6.3 (GND), U8.4 (V-); also elsewhere on the board
PULSE_EN: Q2.1 (G), R8.1, U6.2; also elsewhere on the board
PULSE_EN_N: U6.4; also elsewhere on the board
PULSE_RAIL: Q1.3 (D), R9.1
Q1_G: Q1.1 (G), Q2.3 (D), R7.1
VIN: C1.1, Q1.2 (S), R7.2; also elsewhere on the board
VREF: C23.1, TP2.1, U8.1, U8.2 (-); also elsewhere on the board
VREF_DIV: C13.1, R5.2, R6.1, U8.3 (+)

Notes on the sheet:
Découplage
Polarisation VREF
Rail d'impulsion
PULSE_EN ferme Q1 par Q2 ; R7 le rouvre en moins d'une microseconde ; 10 ohms vers le bus des cellules.

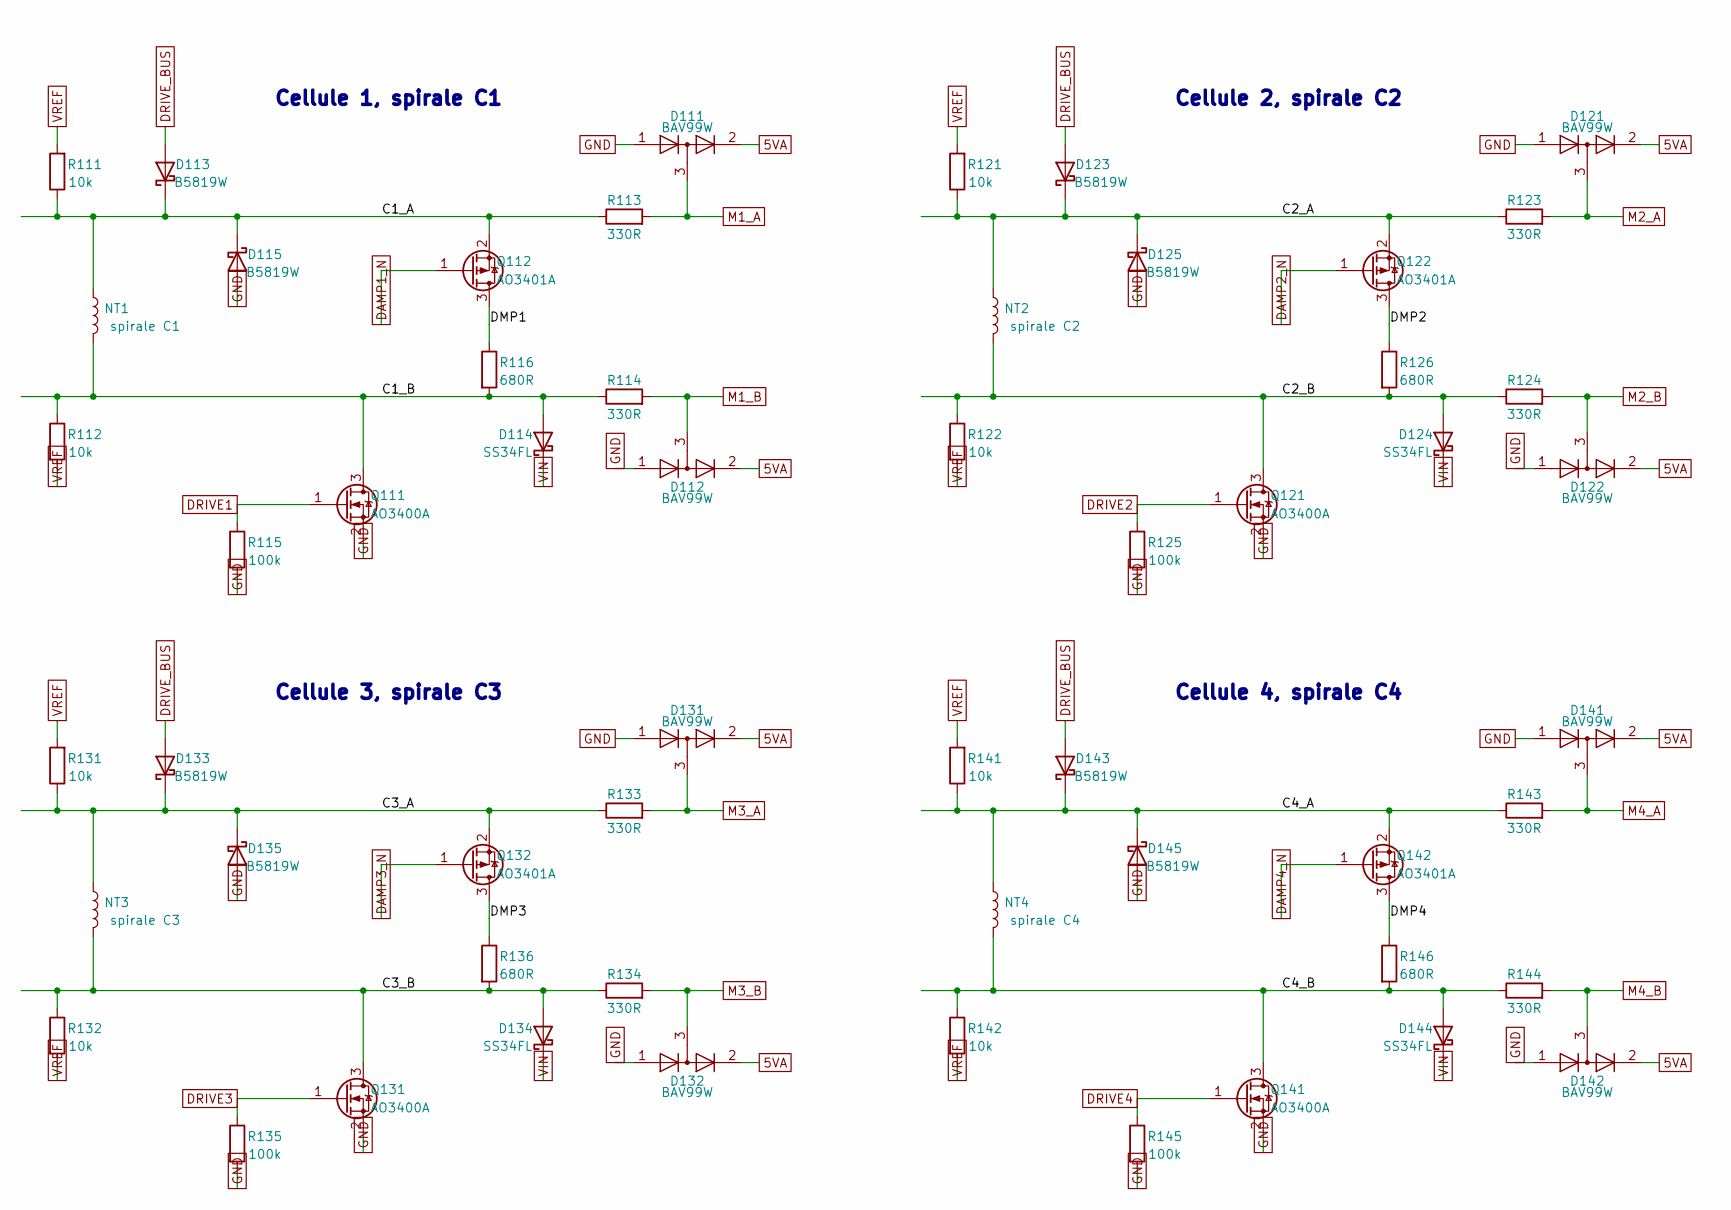
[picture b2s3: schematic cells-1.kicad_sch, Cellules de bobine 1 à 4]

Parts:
D111, D112, D121, D122, D131, D132, D141, D142: BAV99W; SOT-323_SC-70; MPN BAV99W
D113, D115, D123, D125, D133, D135, D143, D145: B5819W; D_SOD-123; MPN B5819W; LCSC C8598
D114, D124, D134, D144: SS34FL; D_SOD-123F; MPN SS34FL; LCSC C2480216
NT1: spirale C1; COIL_TIE
NT2: spirale C2; COIL_TIE
NT3: spirale C3; COIL_TIE
NT4: spirale C4; COIL_TIE
Q111, Q121, Q131, Q141: AO3400A; SOT-23; MPN AO3400A; LCSC C20917
Q112, Q122, Q132, Q142: AO3401A; SOT-23; MPN AO3401A; LCSC C15127
R111, R112, R121, R122, R131, R132, R141, R142: 10k; R_0603_1608Metric
R113, R114, R123, R124, R133, R134, R143, R144: 330R; R_0603_1608Metric
R115, R125, R135, R145: 100k; R_0402_1005Metric
R116, R126, R136, R146: 680R; R_0805_2012Metric

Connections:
5VA: D111.2 (A), D112.2 (A), D121.2 (A), D122.2 (A), D131.2 (A), D132.2 (A), D141.2 (A), D142.2 (A); also elsewhere on the board
C1_A: D113.1 (K), D115.1 (K), NT1.1, Q112.2 (S), R111.1, R113.1
C1_B: D114.2 (A), NT1.2, Q111.3 (D), R112.1, R114.1, R116.2
C2_A: D123.1 (K), D125.1 (K), NT2.1, Q122.2 (S), R121.1, R123.1
C2_B: D124.2 (A), NT2.2, Q121.3 (D), R122.1, R124.1, R126.2
C3_A: D133.1 (K), D135.1 (K), NT3.1, Q132.2 (S), R131.1, R133.1
C3_B: D134.2 (A), NT3.2, Q131.3 (D), R132.1, R134.1, R136.2
C4_A: D143.1 (K), D145.1 (K), NT4.1, Q142.2 (S), R141.1, R143.1
C4_B: D144.2 (A), NT4.2, Q141.3 (D), R142.1, R144.1, R146.2
DAMP1_N: Q112.1 (G); also elsewhere on the board
DAMP2_N: Q122.1 (G); also elsewhere on the board
DAMP3_N: Q132.1 (G); also elsewhere on the board
DAMP4_N: Q142.1 (G); also elsewhere on the board
DMP1: Q112.3 (D), R116.1
DMP2: Q122.3 (D), R126.1
DMP3: Q132.3 (D), R136.1
DMP4: Q142.3 (D), R146.1
DRIVE1: Q111.1 (G), R115.1; also elsewhere on the board
DRIVE2: Q121.1 (G), R125.1; also elsewhere on the board
DRIVE3: Q131.1 (G), R135.1; also elsewhere on the board
DRIVE4: Q141.1 (G), R145.1; also elsewhere on the board
DRIVE_BUS: D113.2 (A), D123.2 (A), D133.2 (A), D143.2 (A); also elsewhere on the board
GND: D111.1 (K), D112.1 (K), D115.2 (A), D121.1 (K), D122.1 (K), D125.2 (A), D131.1 (K), D132.1 (K), D135.2 (A), D141.1 (K), D142.1 (K), D145.2 (A), Q111.2 (S), Q121.2 (S), Q131.2 (S), Q141.2 (S), R115.2, R125.2, R135.2, R145.2; also elsewhere on the board
M1_A: D111.3 (K), R113.2; also elsewhere on the board
M1_B: D112.3 (K), R114.2; also elsewhere on the board
M2_A: D121.3 (K), R123.2; also elsewhere on the board
M2_B: D122.3 (K), R124.2; also elsewhere on the board
M3_A: D131.3 (K), R133.2; also elsewhere on the board
M3_B: D132.3 (K), R134.2; also elsewhere on the board
M4_A: D141.3 (K), R143.2; also elsewhere on the board
M4_B: D142.3 (K), R144.2; also elsewhere on the board
VIN: D114.1 (K), D124.1 (K), D134.1 (K), D144.1 (K); also elsewhere on the board
VREF: R111.2, R112.2, R121.2, R122.2, R131.2, R132.2, R141.2, R142.2; also elsewhere on the board

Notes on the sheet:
Cellule 1, spirale C1
Cellule 2, spirale C2
Cellule 3, spirale C3
Cellule 4, spirale C4
